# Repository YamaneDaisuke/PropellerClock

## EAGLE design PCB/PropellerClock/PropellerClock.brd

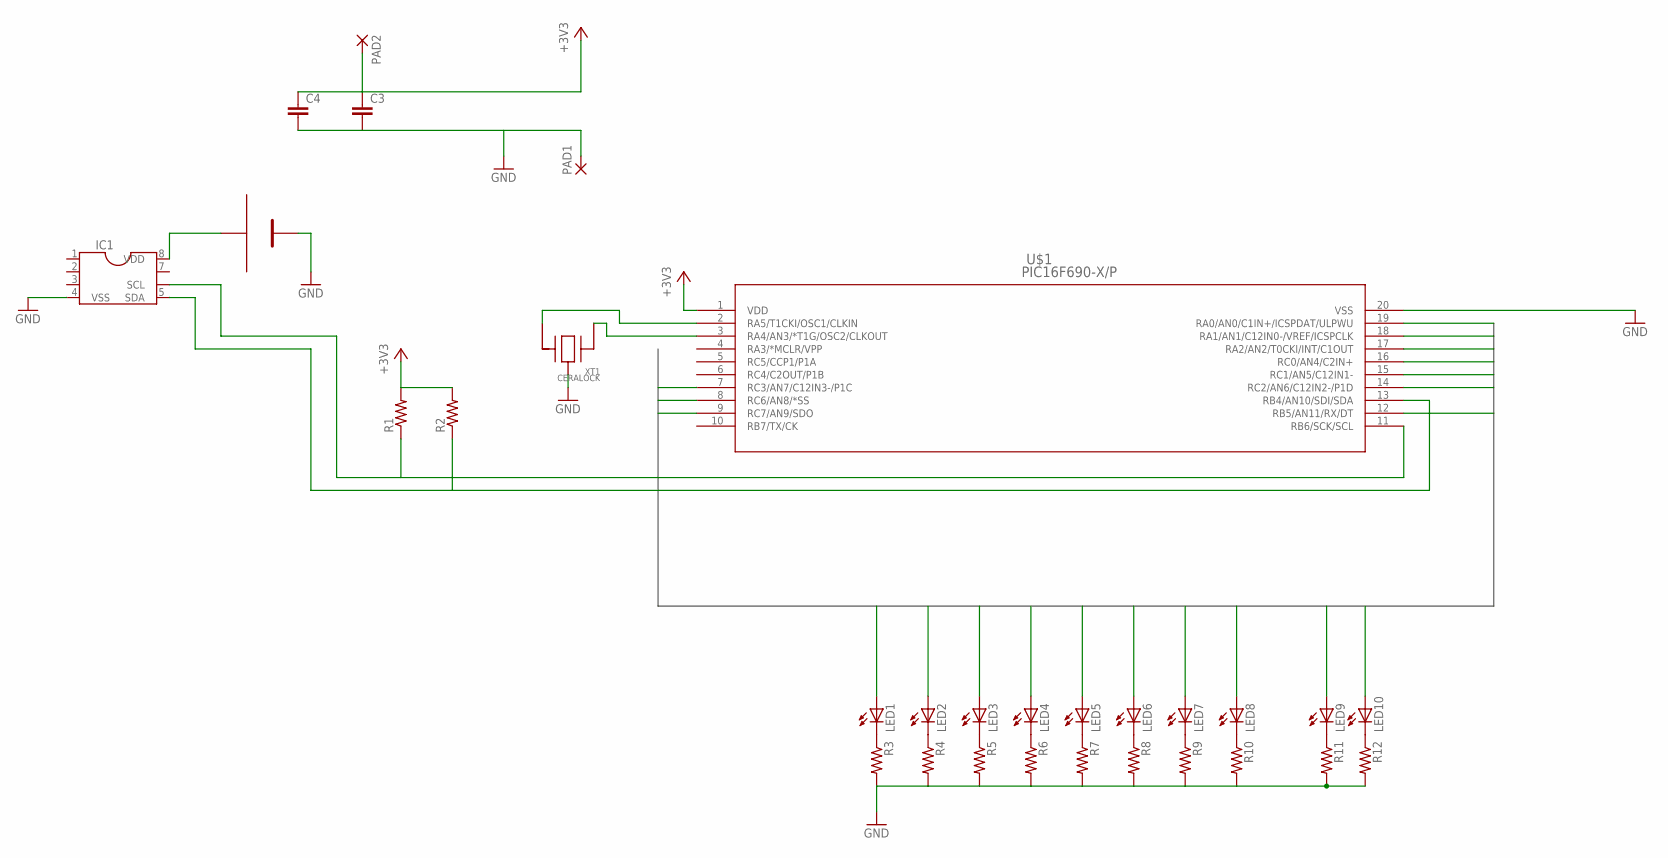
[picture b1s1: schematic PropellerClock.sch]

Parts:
C3, C4: C-EUC2012; C2012
IC1: DIL8S; SOCKET-08
LED1, LED2, LED3, LED4, LED5, LED6, LED7, LED8, LED9, LED10: LED3MM
PAD1, PAD2: 2,54/1,0
R1, R2: R-US_0204/7; 0204/7
R3, R4, R5, R6, R7, R8, R9, R10, R11, R12: R-US_0207/7; 0207/7
U$1: PIC16F690-X/P; PDIP20_300MC
U$2: CR2032-HOLDER2
XT1: CERALOCK

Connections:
+3V3: C3.1, C4.1, PAD2.1, R1.2, R2.2, U$1.1 (VDD)
GND: C3.2, C4.2, IC1.4 (VSS), PAD1.1, R3.2, R4.2, R5.2, R6.2, R7.2, R8.2, R9.2, R10.2, R11.2, R12.2, U$1.20 (VSS), U$2.GND, XT1.P$2 (2)
LED_BUS1: LED1.A, U$1.7 (RC3/AN7/C12IN3-/P1C)
LED_BUS2: LED2.A, U$1.19 (RA0/AN0/C1IN+/ICSPDAT/ULPWU)
LED_BUS3: LED3.A, U$1.18 (RA1/AN1/C12IN0-/VREF/ICSPCLK)
LED_BUS4: LED4.A, U$1.17 (RA2/AN2/T0CKI/INT/C1OUT)
LED_BUS5: LED5.A, U$1.16 (RC0/AN4/C2IN+)
LED_BUS6: LED6.A, U$1.15 (RC1/AN5/C12IN1-)
LED_BUS7: LED7.A, U$1.14 (RC2/AN6/C12IN2-/P1D)
LED_BUS8: LED8.A, U$1.12 (RB5/AN11/RX/DT)
LED_BUS9: LED9.A, U$1.8 (RC6/AN8/*SS)
LED_BUS10: LED10.A, U$1.9 (RC7/AN9/SDO)
unnamed: U$1.3 (RA4/AN3/*T1G/OSC2/CLKOUT), XT1.P$1 (1)
unnamed: U$1.2 (RA5/T1CKI/OSC1/CLKIN), XT1.P$3 (3)
unnamed: IC1.8 (VDD), U$2.+3V
unnamed: IC1.5 (SDA), R2.1, U$1.13 (RB4/AN10/SDI/SDA)
unnamed: IC1.6 (SCL), R1.1, U$1.11 (RB6/SCK/SCL)
unnamed: LED1.K (C), R3.1
unnamed: LED2.K (C), R4.1
unnamed: LED3.K (C), R5.1
unnamed: LED4.K (C), R6.1
unnamed: LED5.K (C), R7.1
unnamed: LED6.K (C), R8.1
unnamed: LED7.K (C), R9.1
unnamed: LED8.K (C), R10.1
unnamed: LED9.K (C), R11.1
unnamed: LED10.K (C), R12.1

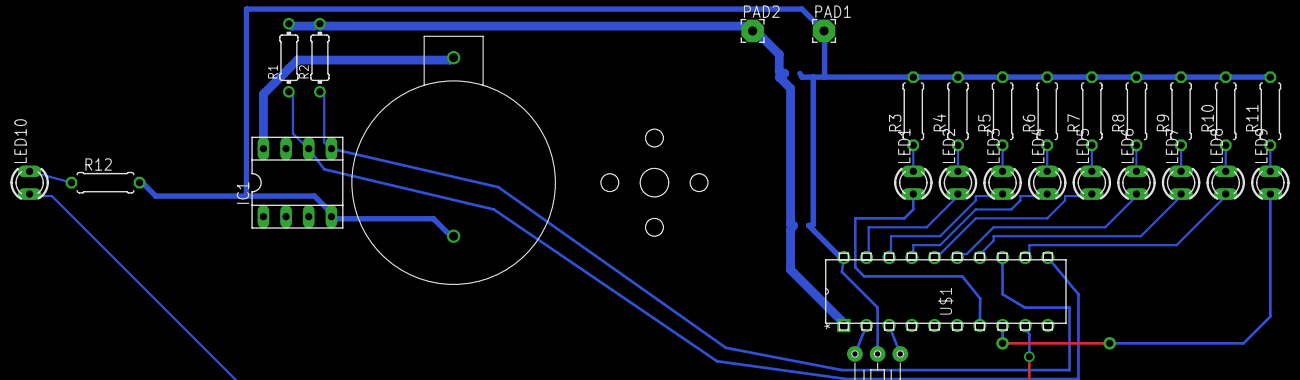
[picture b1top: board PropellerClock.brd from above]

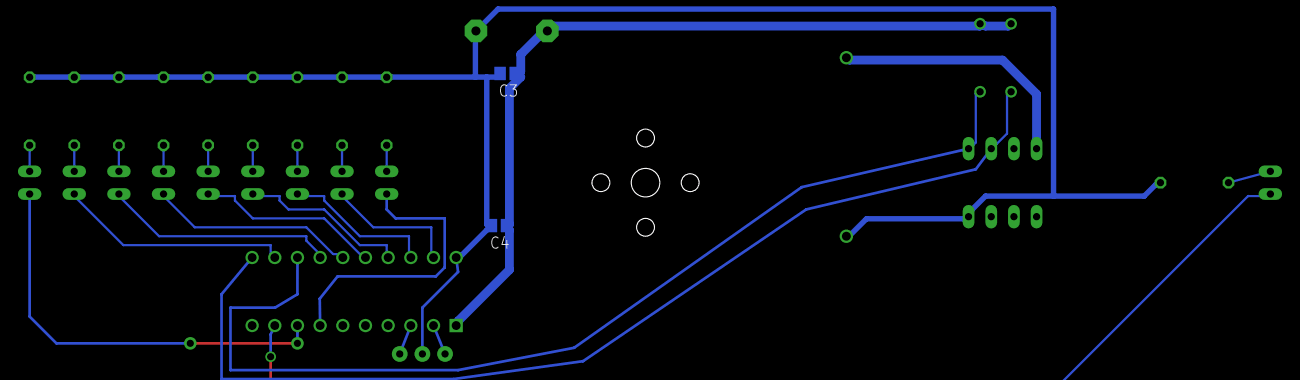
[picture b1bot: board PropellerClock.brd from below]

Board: 2 copper layers, 30 parts (2 on the bottom side), 27 nets.

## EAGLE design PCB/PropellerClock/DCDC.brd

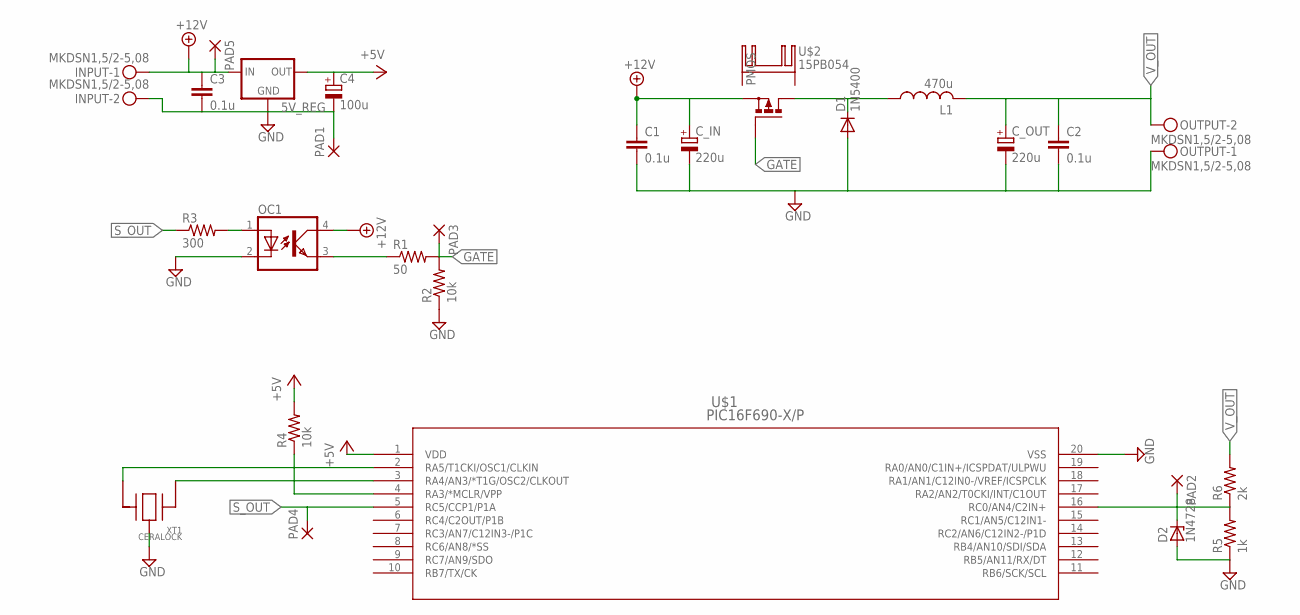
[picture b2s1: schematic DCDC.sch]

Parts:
5V_REG: 78XXS
C1, C2, C3: 0.1u; C050-024X044
C4: 100u; E2,5-6E
C_IN: 220u; E3,5-8
C_OUT: 220u; E3,5-8
D1: 1N5400; DO201-15
D2: 1N4728; DO41Z10
INPUT: MKDSN1,5/2-5,08
L1: 470u; TCV-471M-9A-8026
OC1: PC817; DIL04
OUTPUT: MKDSN1,5/2-5,08
PAD1, PAD2, PAD3, PAD4, PAD5: 2,54/0,8
PMOS: PMOSFET_PTO220BV; TO220BV
R1: 50; 0207/7
R2, R4: 10k; 0207/7
R3: 300; 0207/7
R5: 1k; 0207/10
R6: 2k; 0207/7
U$1: PIC16F690-X/P; PDIP20_300MC
U$2: 15PB054
XT1: CERALOCK

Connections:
+5V: 5V_REG.OUT, C4.+, R4.2, U$1.1 (VDD)
+12V: 5V_REG.IN, C1.1, C3.1, C_IN.+, INPUT.1, OC1.4 (COL), PAD5.1, PMOS.S
GATE: PAD3.1, PMOS.G, R1.2, R2.2
GND: 5V_REG.GND, C1.2, C2.2, C3.2, C4.-, C_IN.-, C_OUT.-, D1.A, D2.A, INPUT.2, OC1.2 (C), OUTPUT.1, PAD1.1, R2.1, R5.1, U$1.20 (VSS), XT1.P$2 (2)
unnamed: OC1.3 (EMIT), R1.1
unnamed: OC1.1 (A), R3.2
unnamed: U$1.2 (RA5/T1CKI/OSC1/CLKIN), XT1.P$3 (3)
unnamed: U$1.3 (RA4/AN3/*T1G/OSC2/CLKOUT), XT1.P$1 (1)
unnamed: R4.1, U$1.4 (RA3/*MCLR/VPP)
unnamed: D1.C, L1.P$1 (1), PMOS.D
S_OUT: PAD4.1, R3.1, U$1.5 (RC5/CCP1/P1A)
V_IN: D2.C, PAD2.1, R5.2, R6.1, U$1.16 (RC0/AN4/C2IN+)
V_OUT: C2.1, C_OUT.+, L1.P$2 (2), OUTPUT.2, R6.2

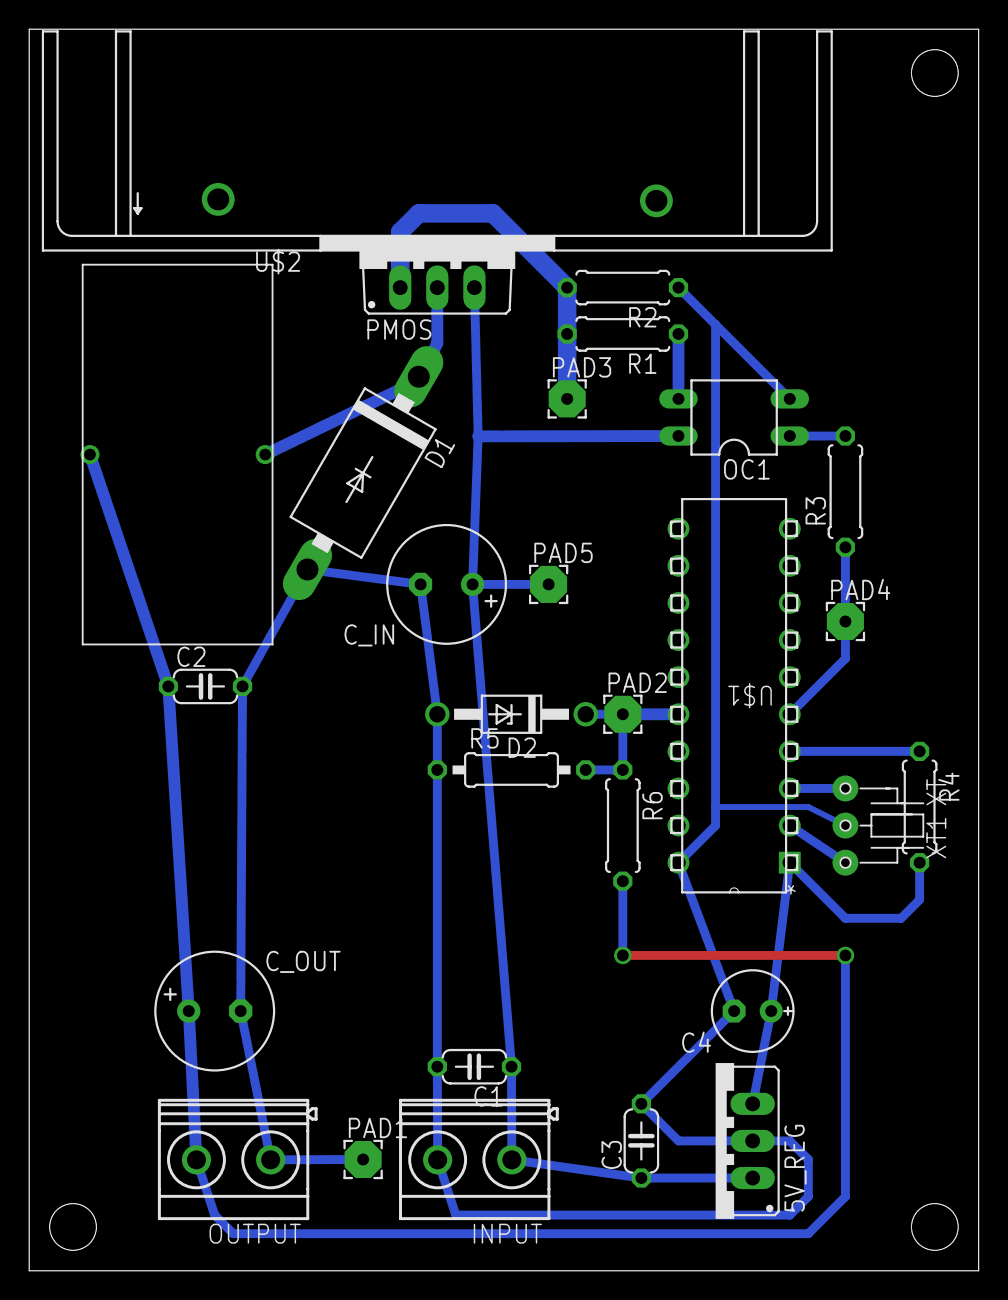
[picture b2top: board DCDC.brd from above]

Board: 2 copper layers, 65.0 x 85.0 mm, 28 parts (0 on the bottom side), 13 nets.

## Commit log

2016-08-07 gitignoreを更新
2016-08-16 add PCB project
2016-08-16 基板第一弾完成
2016-10-21 DCDCを追加
2016-10-22 デバックピン取り付け用の穴を追加 PICの入力保護用のツェナーダイオードを追加
2016-10-28 FETをNMOSからPMOSに変更
2016-10-28 プロペラ部の回路を作成
2016-11-01 PropellerClock本体用プロジェクトの作成
2016-11-01 DCDC制御用プロジェクトの作成
2016-11-01 DCDC制御プログラムの雛形完成
    コミットの詳細
    PWMモジュールの実装
    AnalogInの実装
    P制御の導入
